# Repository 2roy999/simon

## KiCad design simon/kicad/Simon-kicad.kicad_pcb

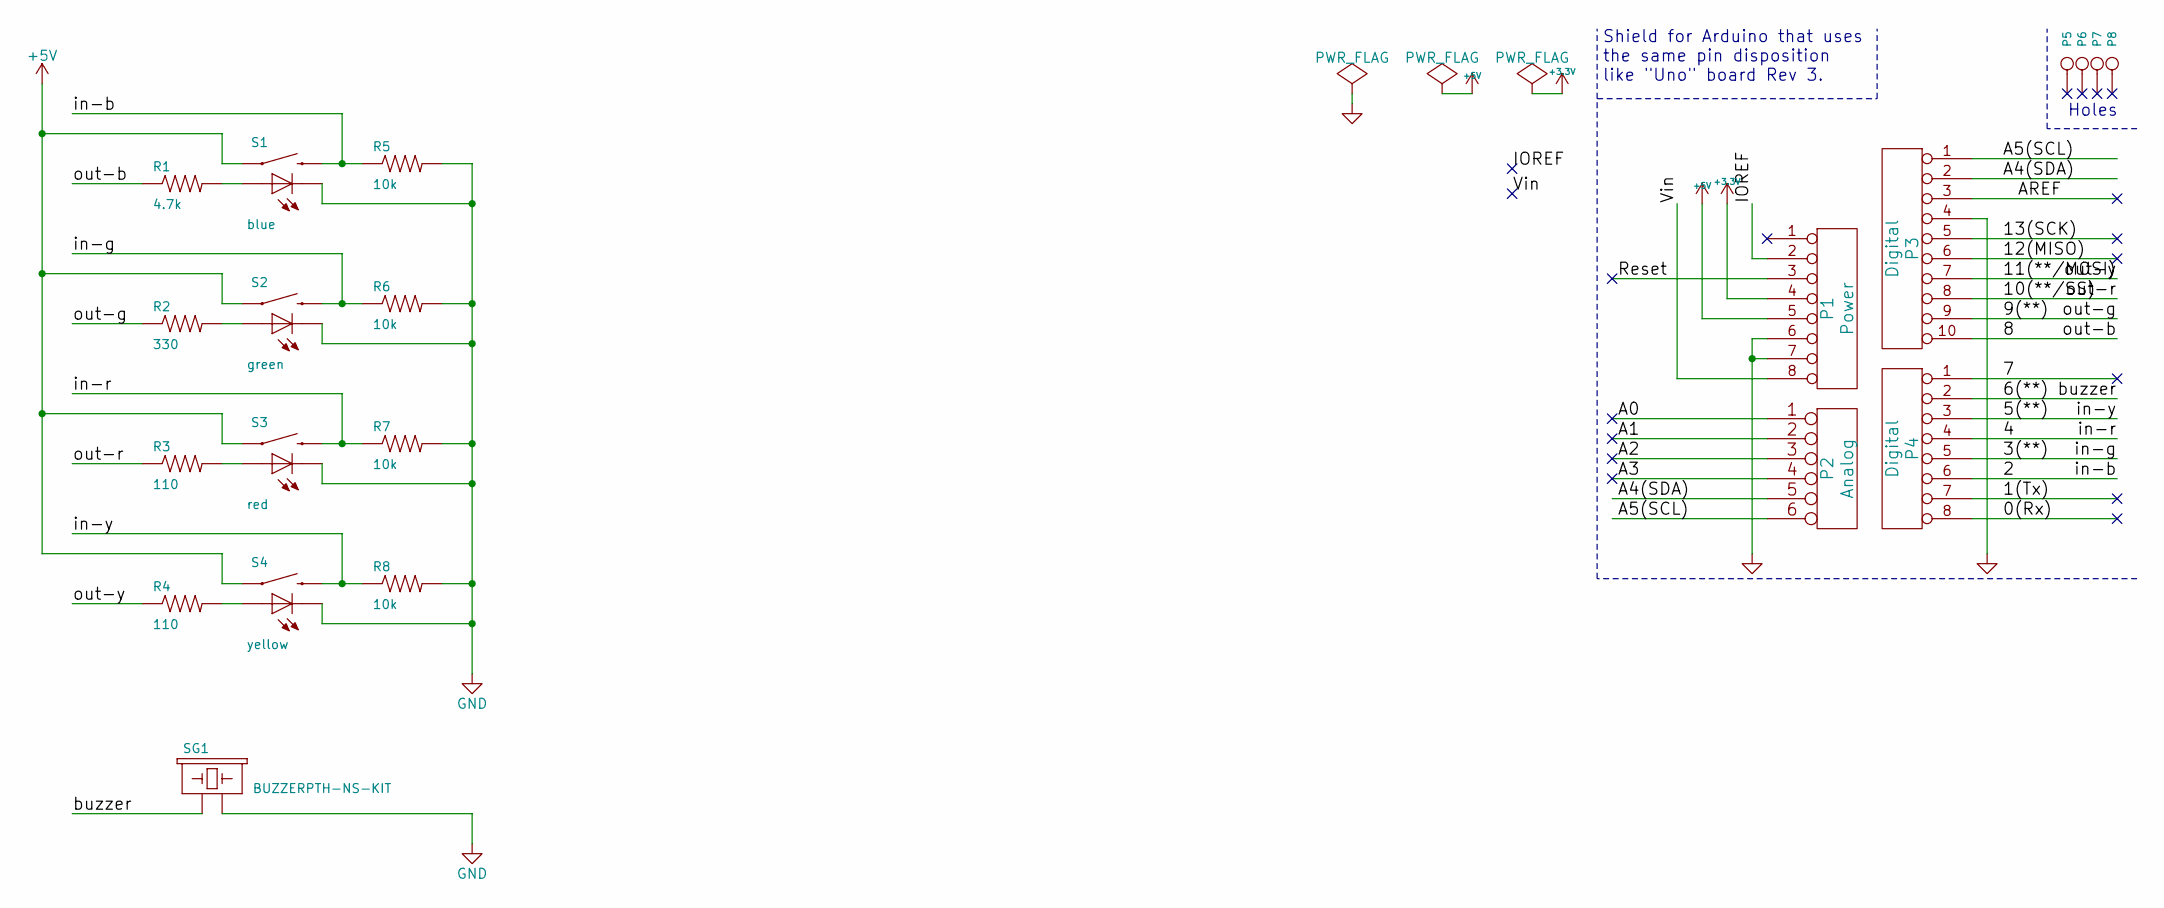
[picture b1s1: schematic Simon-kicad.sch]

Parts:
P1: Power; Socket_Strip_Arduino_1x08
P2: Analog; Socket_Strip_Arduino_1x06
P3: Digital; Socket_Strip_Arduino_1x10
P4: Digital; Socket_Strip_Arduino_1x08
P5, P6, P7, P8: CONN_1; Arduino_1pin
R1: 4.7k; SparkFun-Resistors-AXIAL-0.4
R2: 330; SparkFun-Resistors-AXIAL-0.4
R3, R4: 110; SparkFun-Resistors-AXIAL-0.4
R5, R6, R7, R8: 10k; SparkFun-Resistors-AXIAL-0.4
S1: blue; SparkFun-Electromechanical-TACTILE-PTH-LED-12MM
S2: green; SparkFun-Electromechanical-TACTILE-PTH-LED-12MM
S3: red; SparkFun-Electromechanical-TACTILE-PTH-LED-12MM
S4: yellow; SparkFun-Electromechanical-TACTILE-PTH-LED-12MM
SG1: BUZZERPTH-NS-KIT; SparkFun-Electromechanical-BUZZER-12MM-NS

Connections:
+3V3: P1.4
+5V: P1.5, S1.4 (1), S2.4 (1), S3.4 (1), S4.4 (1)
/0(Rx): P4.8
/1(Tx): P4.7
/2: P4.6, R5.P$1 (1), S1.2
/3(**): P4.5, R6.P$1 (1), S2.2
/4: P4.4, R7.P$1 (1), S3.2
/5(**): P4.3, R8.P$1 (1), S4.2
/6(**): P4.2, SG1.+ (1)
/7: P4.1
/8: P3.10, R1.P$1 (1)
/9(**): P3.9, R2.P$1 (1)
/10(**/SS): P3.8, R3.P$1 (1)
/11(**/MOSI): P3.7, R4.P$1 (1)
/12(MISO): P3.6
/13(SCK): P3.5
/A0: P2.1
/A1: P2.2
/A2: P2.3
/A3: P2.4
/A4(SDA): P2.5, P3.2
/A5(SCL): P2.6, P3.1
/AREF: P3.3
/IOREF: P1.2
/Reset: P1.3
/Vin: P1.8
GND: P1.6, P1.7, P3.4, R5.P$2 (2), R6.P$2 (2), R7.P$2 (2), R8.P$2 (2), S1.C, S2.C, S3.C, S4.C, SG1.- (2)
unnamed: R1.P$2 (2), S1.A
unnamed: R2.P$2 (2), S2.A
unnamed: R3.P$2 (2), S3.A
unnamed: R4.P$2 (2), S4.A

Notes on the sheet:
Holes
Shield for Arduino that uses the same pin disposition like "Uno" board Rev 3.

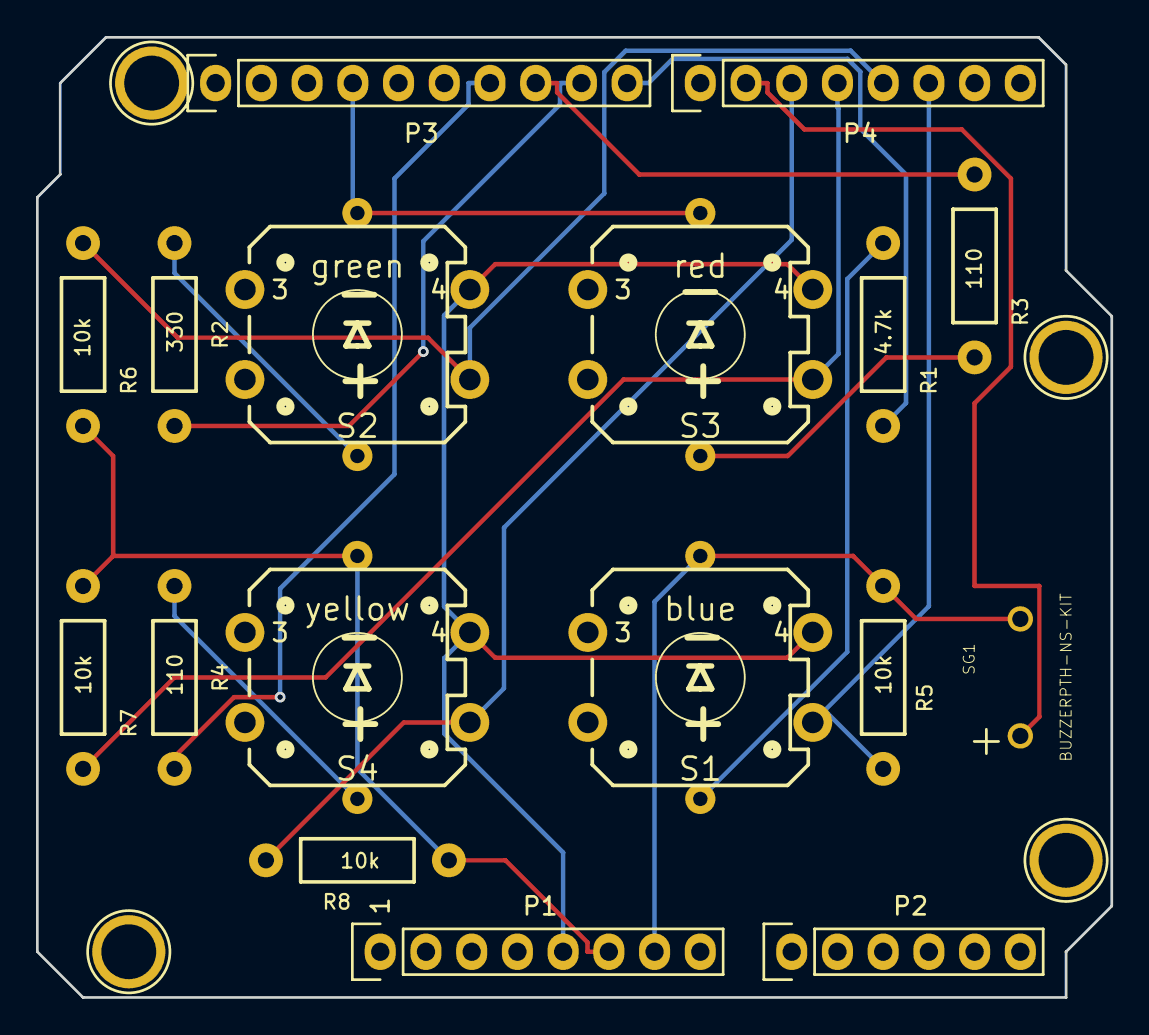
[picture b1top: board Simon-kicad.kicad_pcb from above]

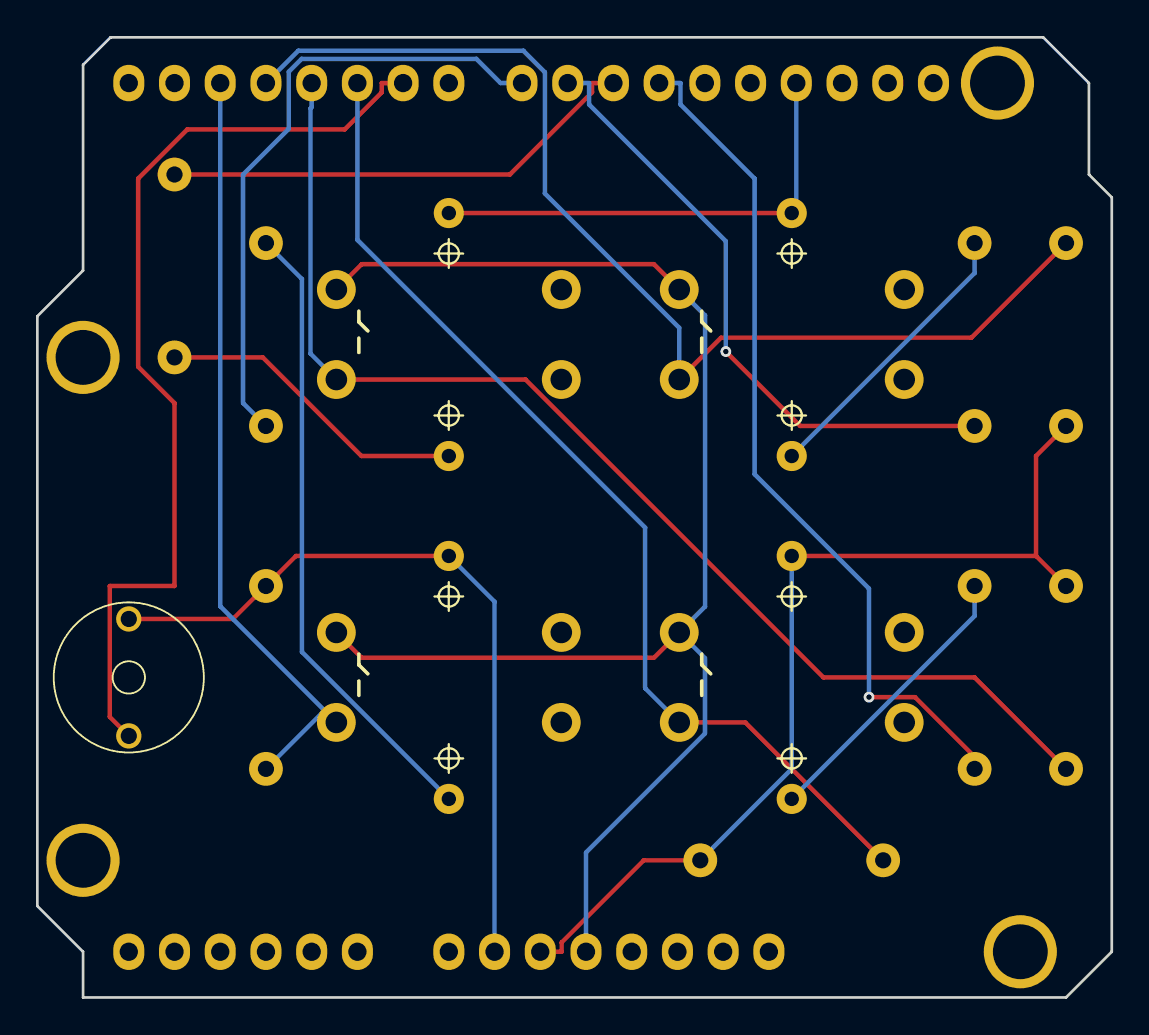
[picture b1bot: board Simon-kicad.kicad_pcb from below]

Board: 2 copper layers, 59.7 x 53.3 mm, 21 parts (13 on the bottom side), 17 nets.

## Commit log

2019-02-06 simon
